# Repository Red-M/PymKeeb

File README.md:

# PymKeeb
## What is this?
I'm getting fed up with the options for keyboards and there isn't anything that I want 100%, everything is a compromise between form factor, customizability and availability.
So I'm making my own keyboard.

## Design choices
I don't want to limit end users on customizing their boards or choosing what they want, so I'll be maximumizing that as much as possible while also giving the option for changing things like the size and layout in forks or derivatives.
I don't want the host device to make choices for the user so limiting things behind having a certain OS is not ok, eg, software that runs on the host device.

## Goals
- USB C input
    - This is just a requirement at this point
- Layout
    - Full size layout with 4 extra switches above the numpad to set for macros
    - Indicator lights need to be above the numbpad
    - Two LEDs per switch, I want extra light
- Switches
    - Hot swap switches
        - Khali hotswaps allow for MX style switches to swap in and out
            - Has a number of switch variants that will fit
- Firmware/Software
    - Firmware only, no host device software at all.
    - Firmware updates should be really simple, no custom software, just drag and drop in DFU or similar
    - CapsLock indicator is in key and matches RGB light of switch
    - All on keyboard with function key similar to ducky keyboards
    - Brightness toggle
    - Macro support
    - NKRO
        - I don't want artifacts or ghosting at all

## Software for designing/building the board
KiCAD, you're going to need KiCAD.
I'm also learning KiCAD so please if you see something I've done that could be done a better way, please file at least an issue or go a head and fix it in a PR.
If it makes sense, I'll merge it in, no questions asked.

## Firmware
This is largely going to depend on what MCU I choose and right now all I know is that the pico or an STMF4 might be the best options.

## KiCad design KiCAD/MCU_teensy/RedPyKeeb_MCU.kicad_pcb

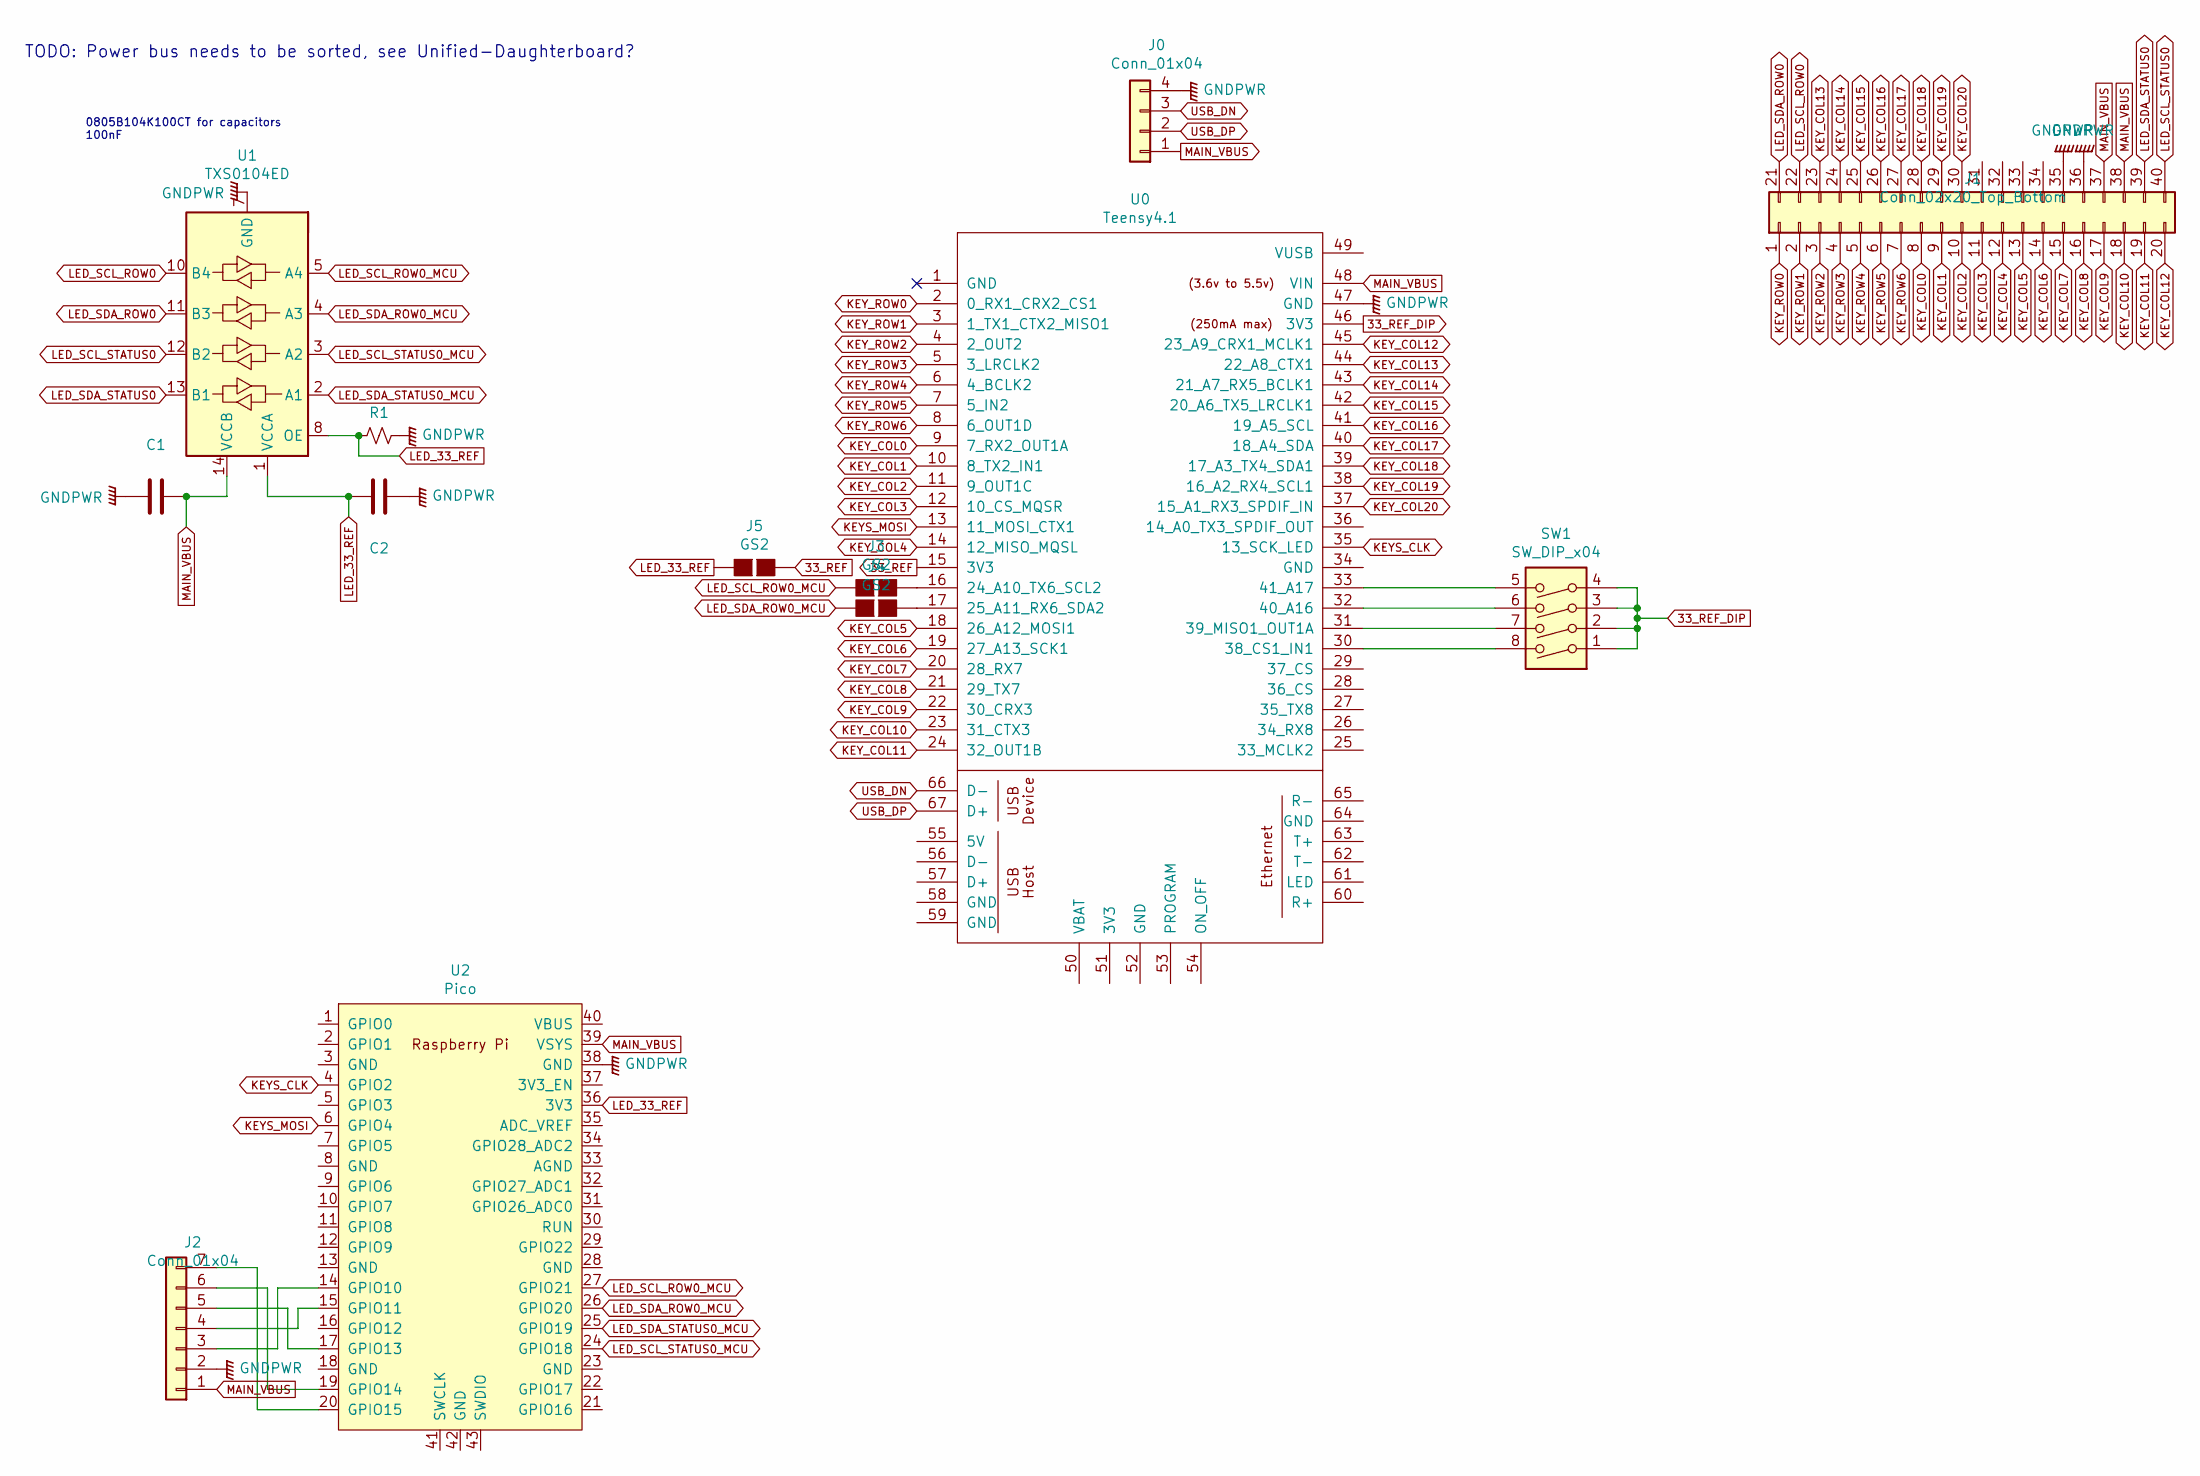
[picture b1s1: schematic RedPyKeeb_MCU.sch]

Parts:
C1, C2: 0805B101K100CT; C_0805_2012Metric_Pad1.18x1.45mm_HandSolder; Mouser No 791-0805B101K100CT
J0: Conn_01x04; JST_EH_S4B-EH_1x04_P2.50mm_Horizontal; Mouser No 485-3955
J1: Conn_02x20_Top_Bottom; PinHeader_2x20_P2.54mm_Vertical_SMD_doublesided; Mouser No 649-95278-102-40LF
J2: Conn_01x04; JST_EH_S7B-EH_1x07_P2.50mm_Horizontal; Mouser No 485-3955
J3, J4, J5: GS2
R1: ERJ-6RED2003V; R_0805_HandSoldering; Mouser No 667-ERJ-6RED2003V
SW1: SW_DIP_x04; SW_DIP_x4_W8.61mm_Slide_LowProfile_bothsides; Mouser No 653-A6SN-4104
U0: Teensy4.1; Teensy41; Mouser No 474-DEV-16771
U1: TXS0104ED; SOIC-14_3.9x8.7mm_P1.27mm; Mouser No 595-TXS0104ED
U2: Pico; RPi_Pico_SMD_TH

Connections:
33_REF: J5.1 (G1), U0.15 (3V3)
33_REF_DIP: SW1.1, SW1.2, SW1.3, SW1.4, U0.46 (3V3)
GNDPWR: C1.1, C2.1, J0.4, J1.35, J1.36, J2.2, R1.1, U0.47 (GND), U1.7 (GND), U2.38 (GND)
KEYS_CLK: U0.35 (13_SCK_LED), U2.4 (GPIO2)
KEYS_MOSI: U0.13 (11_MOSI_CTX1), U2.6 (GPIO4)
KEY_COL0: J1.8, U0.9 (7_RX2_OUT1A)
KEY_COL1: J1.9, U0.10 (8_TX2_IN1)
KEY_COL2: J1.10, U0.11 (9_OUT1C)
KEY_COL3: J1.11, U0.12 (10_CS_MQSR)
KEY_COL4: J1.12, U0.14 (12_MISO_MQSL)
KEY_COL5: J1.13, U0.18 (26_A12_MOSI1)
KEY_COL6: J1.14, U0.19 (27_A13_SCK1)
KEY_COL7: J1.15, U0.20 (28_RX7)
KEY_COL8: J1.16, U0.21 (29_TX7)
KEY_COL9: J1.17, U0.22 (30_CRX3)
KEY_COL10: J1.18, U0.23 (31_CTX3)
KEY_COL11: J1.19, U0.24 (32_OUT1B)
KEY_COL12: J1.20, U0.45 (23_A9_CRX1_MCLK1)
KEY_COL13: J1.23, U0.44 (22_A8_CTX1)
KEY_COL14: J1.24, U0.43 (21_A7_RX5_BCLK1)
KEY_COL15: J1.25, U0.42 (20_A6_TX5_LRCLK1)
KEY_COL16: J1.26, U0.41 (19_A5_SCL)
KEY_COL17: J1.27, U0.40 (18_A4_SDA)
KEY_COL18: J1.28, U0.39 (17_A3_TX4_SDA1)
KEY_COL19: J1.29, U0.38 (16_A2_RX4_SCL1)
KEY_COL20: J1.30, U0.37 (15_A1_RX3_SPDIF_IN)
KEY_ROW0: J1.1, U0.2 (0_RX1_CRX2_CS1)
KEY_ROW1: J1.2, U0.3 (1_TX1_CTX2_MISO1)
KEY_ROW2: J1.3, U0.4 (2_OUT2)
KEY_ROW3: J1.4, U0.5 (3_LRCLK2)
KEY_ROW4: J1.5, U0.6 (4_BCLK2)
KEY_ROW5: J1.6, U0.7 (5_IN2)
KEY_ROW6: J1.7, U0.8 (6_OUT1D)
LED_33_REF: C2.2, J5.2 (G2), R1.2, U1.1 (VCCA), U1.8 (OE), U2.36 (3V3)
LED_SCL_ROW0: J1.22, U1.10 (B4)
LED_SCL_ROW0_MCU: J3.2 (G2), U1.5 (A4), U2.27 (GPIO21)
LED_SCL_STATUS0: J1.40, U1.12 (B2)
LED_SCL_STATUS0_MCU: U1.3 (A2), U2.24 (GPIO18)
LED_SDA_ROW0: J1.21, U1.11 (B3)
LED_SDA_ROW0_MCU: J4.2 (G2), U1.4 (A3), U2.26 (GPIO20)
LED_SDA_STATUS0: J1.39, U1.13 (B1)
LED_SDA_STATUS0_MCU: U1.2 (A1), U2.25 (GPIO19)
MAIN_VBUS: C1.2, J0.1, J1.37, J1.38, J2.1, U0.48 (VIN), U1.14 (VCCB), U2.39 (VSYS)
unnamed: J2.3, U2.14 (GPIO10)
unnamed: J2.4, U2.15 (GPIO11)
unnamed: J2.5, U2.17 (GPIO13)
unnamed: J2.6, U2.19 (GPIO14)
unnamed: J2.7, U2.20 (GPIO15)
unnamed: J3.1 (G1), U0.16 (24_A10_TX6_SCL2)
unnamed: J4.1 (G1), U0.17 (25_A11_RX6_SDA2)
unnamed: SW1.5, U0.33 (41_A17)
unnamed: SW1.6, U0.32 (40_A16)
unnamed: SW1.7, U0.31 (39_MISO1_OUT1A)
unnamed: SW1.8, U0.30 (38_CS1_IN1)
USB_DN: J0.3, U0.66 (D-)
USB_DP: J0.2, U0.67 (D+)

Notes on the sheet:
TODO: Power bus needs to be sorted, see Unified-Daughterboard?
0805B104K100CT for capacitors 100nF

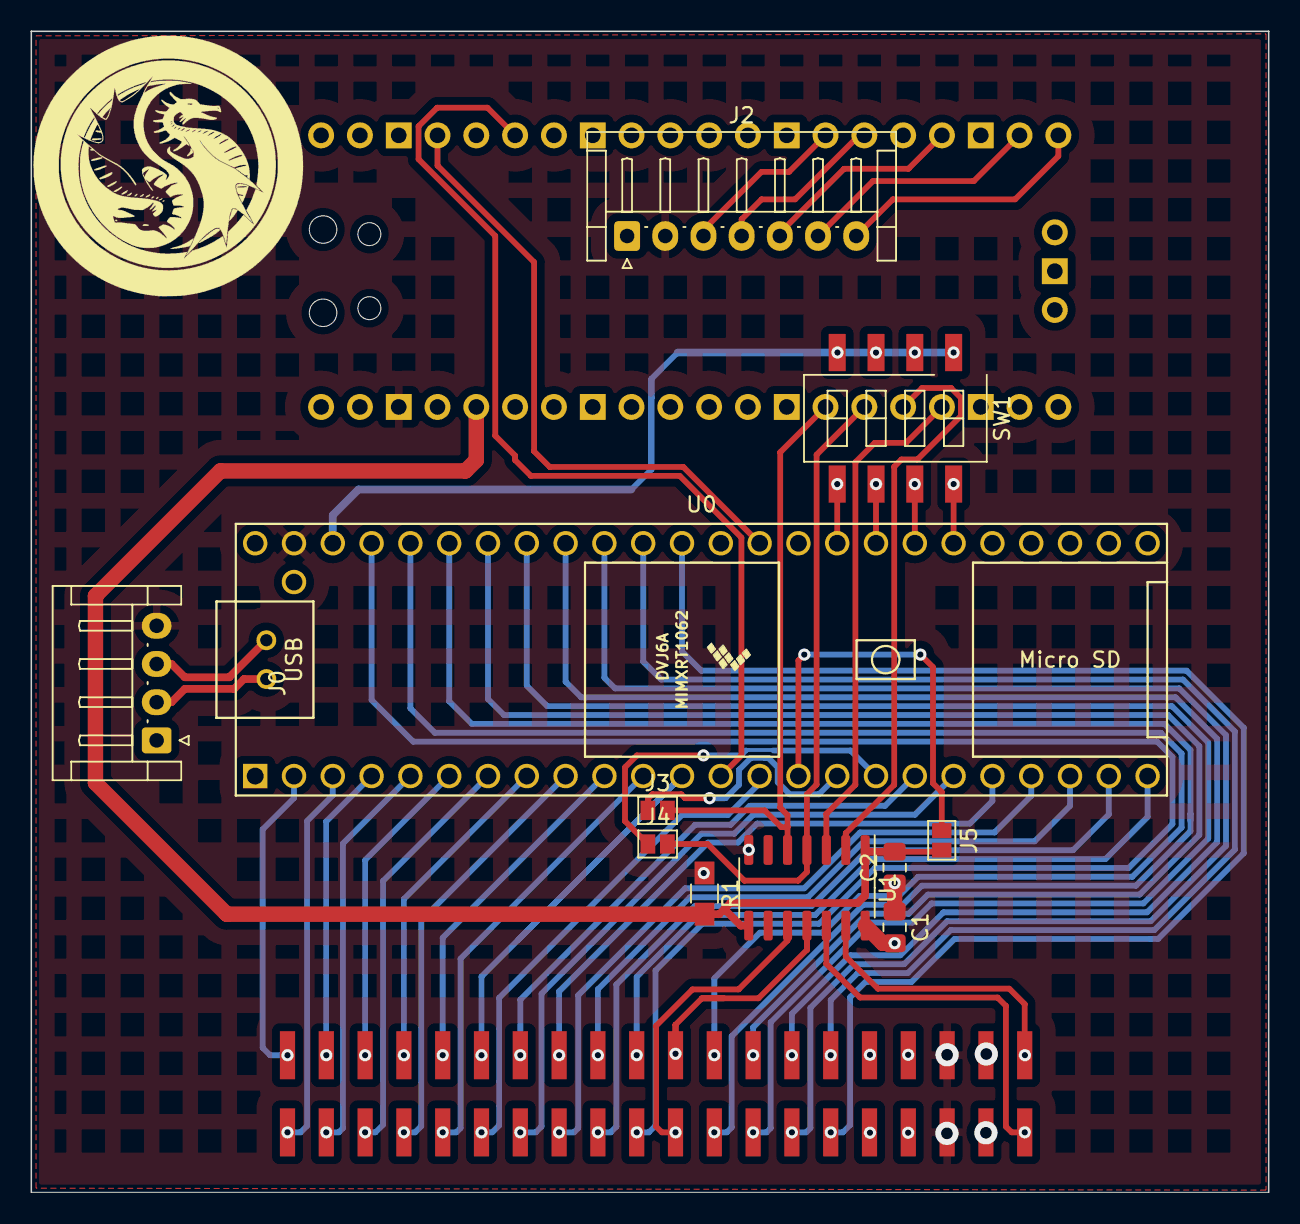
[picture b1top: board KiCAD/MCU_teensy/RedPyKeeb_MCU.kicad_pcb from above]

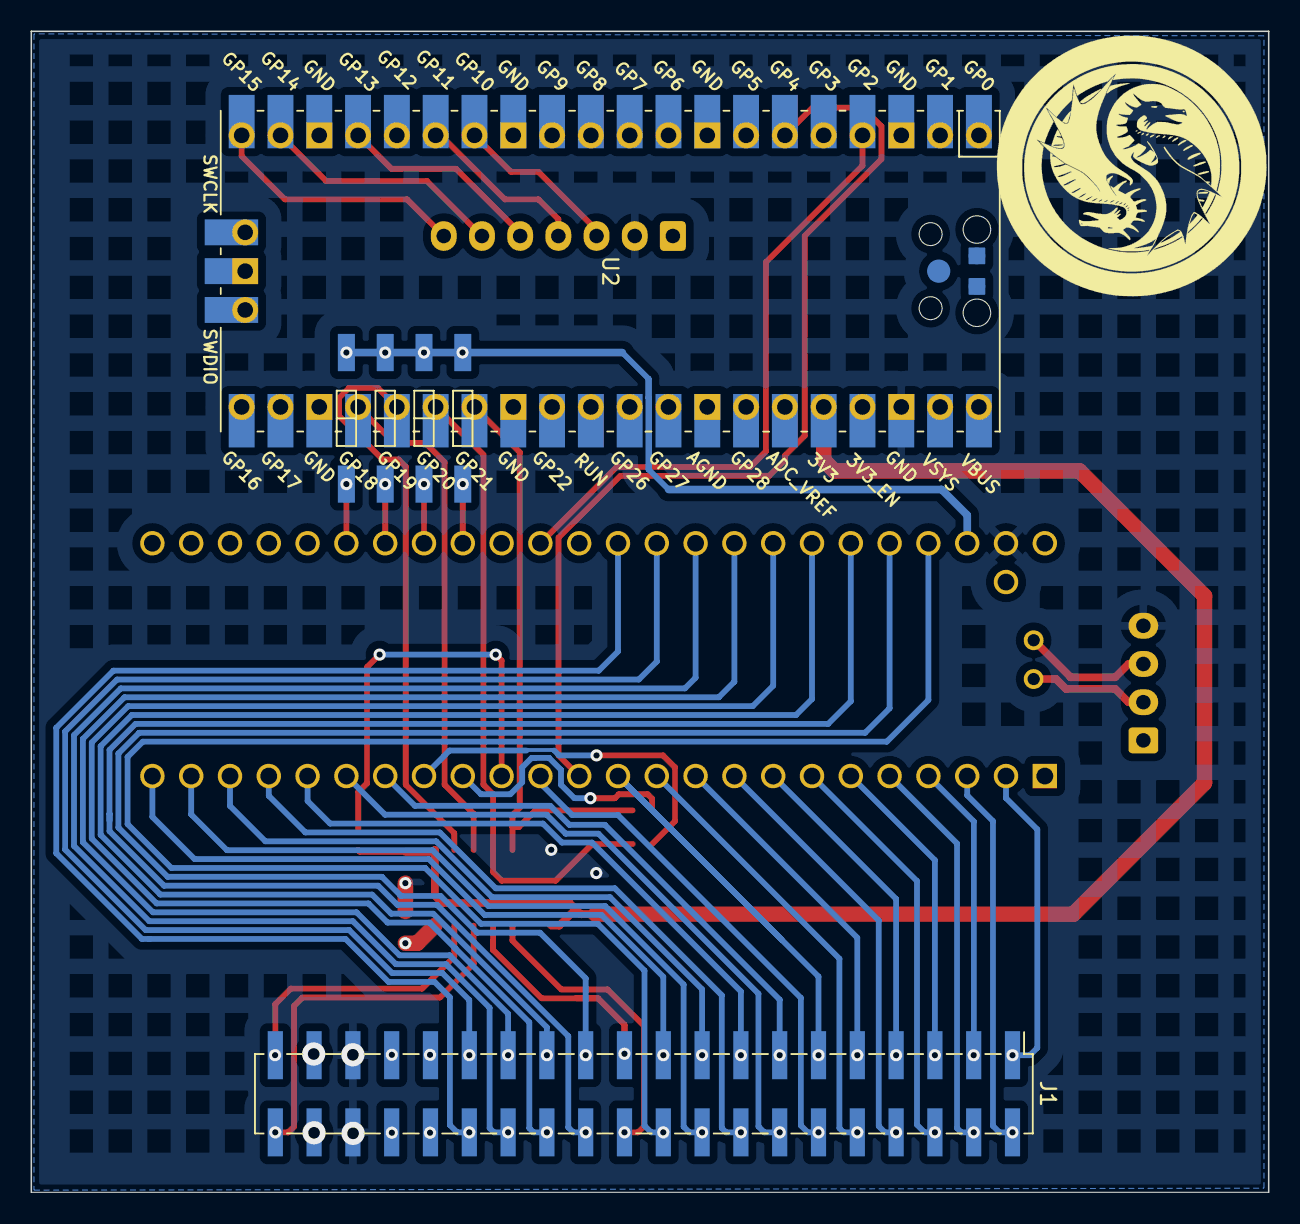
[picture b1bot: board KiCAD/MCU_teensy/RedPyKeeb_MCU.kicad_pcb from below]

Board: 4 copper layers, 81.0 x 76.0 mm, 13 parts (2 on the bottom side), 56 nets.

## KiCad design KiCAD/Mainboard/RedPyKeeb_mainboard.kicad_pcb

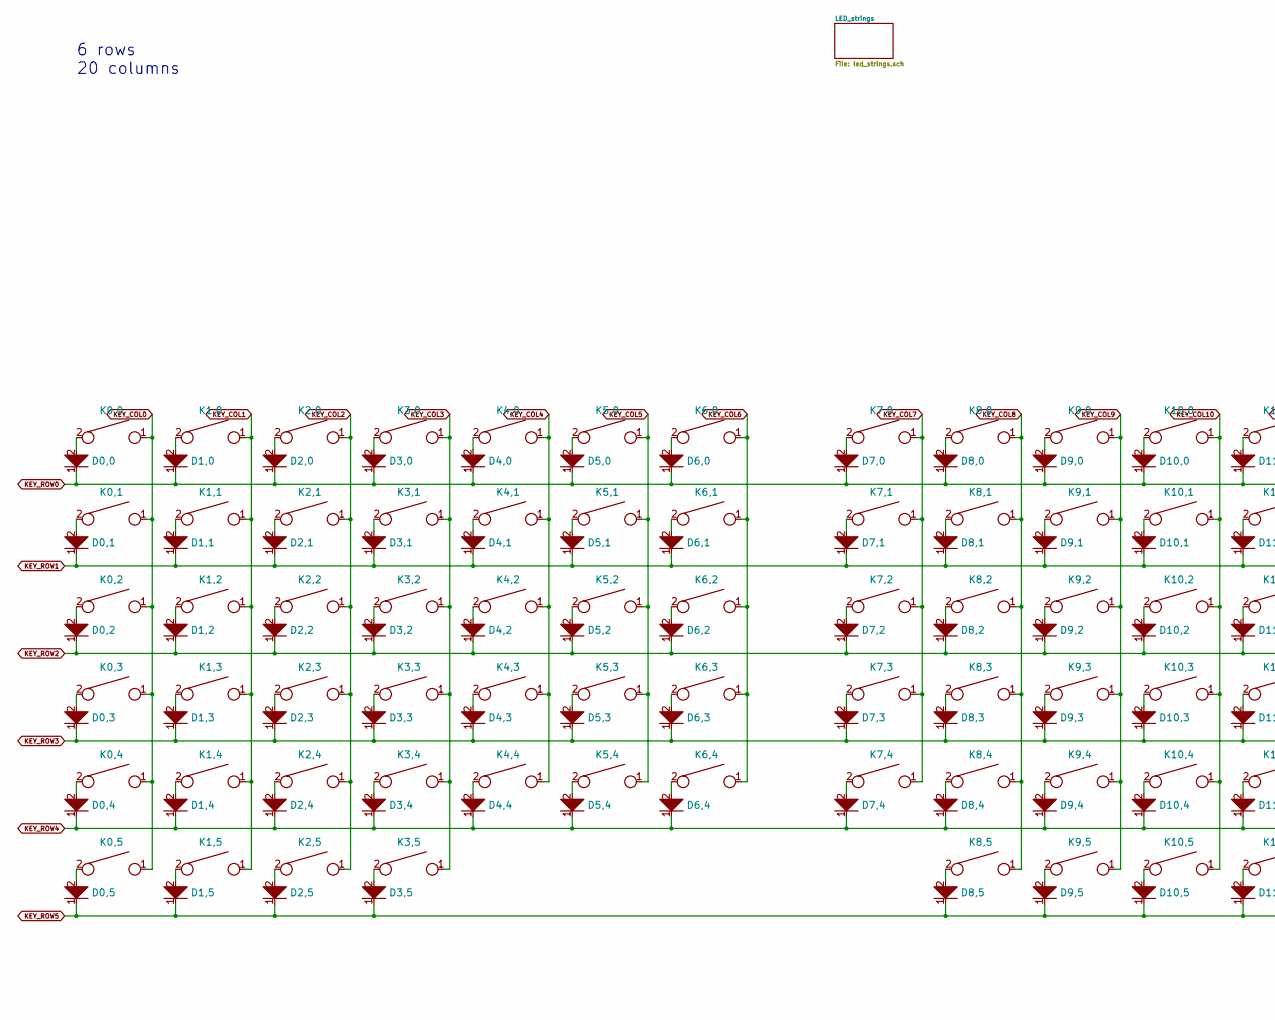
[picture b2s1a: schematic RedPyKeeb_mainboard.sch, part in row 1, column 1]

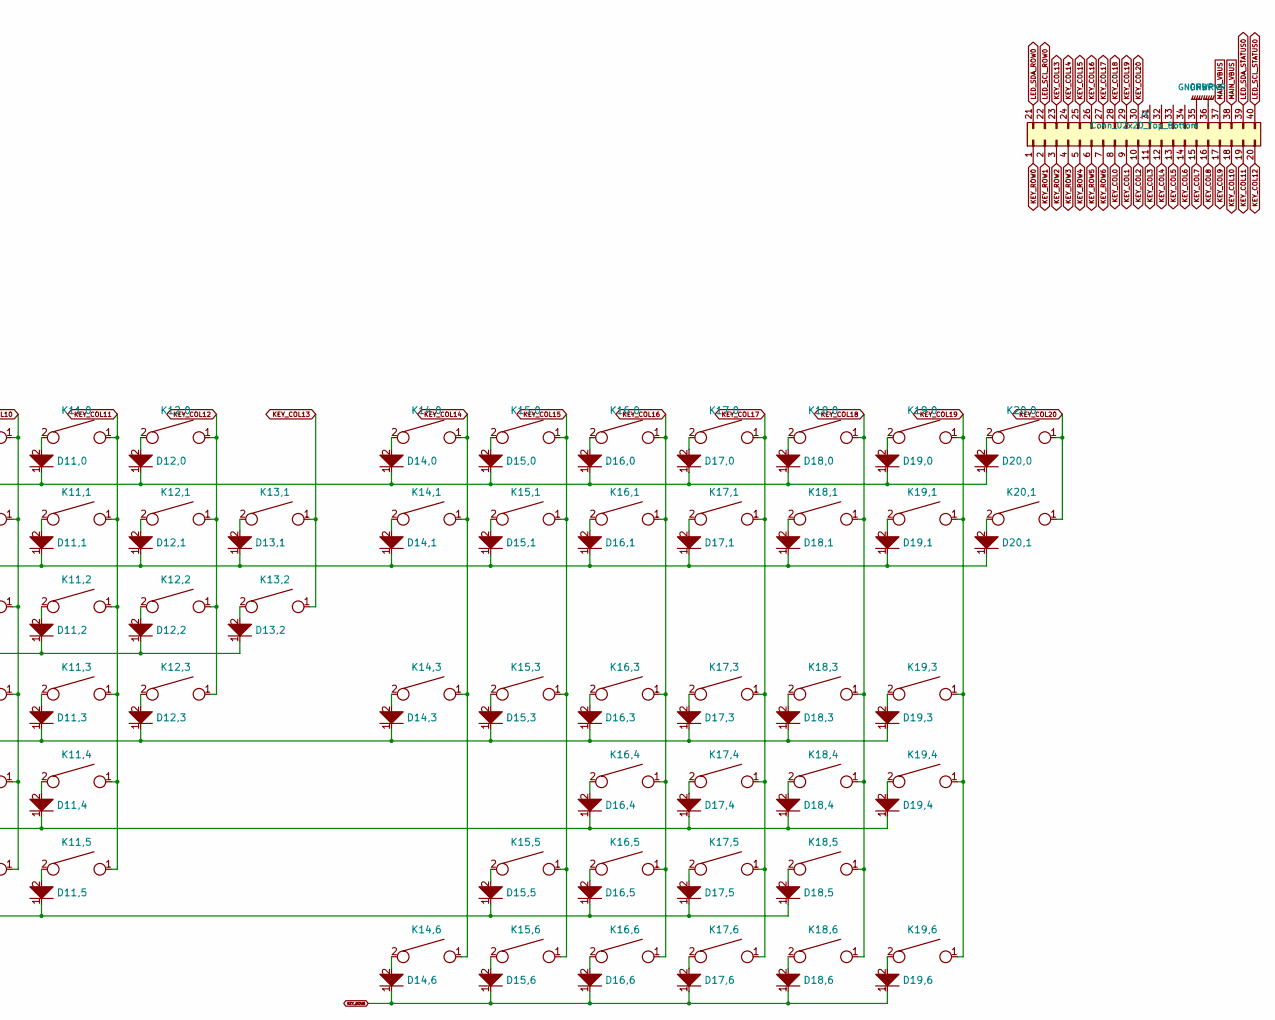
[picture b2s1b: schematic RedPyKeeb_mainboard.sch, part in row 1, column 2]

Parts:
D0,0, D0,1, D0,2, D0,3, D0,4, D0,5, D1,0, D1,1, D1,2, D1,3, D1,4, D1,5, D2,0, D2,1, D2,2, D2,3, D2,4, D2,5, D3,0, D3,1, D3,2, D3,3, D3,4, D3,5, D4,0, D4,1, D4,2, D4,3, D4,4, D5,0, D5,1, D5,2, D5,3, D5,4, D6,0, D6,1, D6,2, D6,3, D6,4, D7,0, D7,1, D7,2, D7,3, D7,4, D8,0, D8,1, D8,2, D8,3, D8,4, D8,5, D9,0, D9,1, D9,2, D9,3, D9,4, D9,5, D10,0, D10,1, D10,2, D10,3, D10,4, D10,5, D11,0, D11,1, D11,2, D11,3, D11,4, D11,5, D12,0, D12,1, D12,2, D12,3, D13,1, D13,2, D14,0, D14,1, D14,3, D14,6, D15,0, D15,1, D15,3, D15,5, D15,6, D16,0, D16,1, D16,3, D16,4, D16,5, D16,6, D17,0, D17,1, D17,3, D17,4, D17,5, D17,6, D18,0, D18,1, D18,3, D18,4, D18,5, D18,6, D19,0, D19,1, D19,3, D19,4, D19,6, D20,0, D20,1: 1N4148W-7-F; D_SOD123_axial; Mouser No 621-1N4148W-F
J1: Conn_02x20_Top_Bottom; PinHeader_2x20_P2.54mm_Vertical_SMD_doublesided; Mouser No 200-SSM120LMDVBE
K0,0, K0,1, K1,0, K1,1, K1,2, K1,3, K1,4, K2,0, K2,1, K2,2, K2,3, K2,4, K3,0, K3,1, K3,2, K3,3, K3,4, K4,0, K4,1, K4,2, K4,3, K4,4, K5,0, K5,1, K5,2, K5,3, K5,4, K6,0, K6,1, K6,2, K6,3, K6,4, K7,0, K7,1, K7,2, K7,3, K7,4, K8,0, K8,1, K8,2, K8,3, K8,4, K9,0, K9,1, K9,2, K9,3, K9,4, K10,0, K10,1, K10,2, K10,3, K10,4, K11,0, K11,1, K11,2, K11,3, K12,0, K12,1, K12,2, K14,0, K14,1, K14,3, K14,6, K15,0, K15,1, K15,3, K15,5, K15,6, K16,0, K16,1, K16,3, K16,4, K16,5, K16,6, K17,0, K17,1, K17,3, K17,4, K17,5, K18,0, K18,1, K18,3, K18,4, K18,5, K18,6, K19,0, K19,1, K19,3, K20,0, K20,1: SW_Hotswap_Kailh_1.00u
K0,2, K13,2: SW_Hotswap_Kailh_1.50u
K0,3: SW_Hotswap_Kailh_1.75u
K0,4, K12,3: SW_Hotswap_Kailh_2.25u
K0,5, K1,5, K2,5, K8,5, K9,5, K10,5, K11,5: SW_Hotswap_Kailh_1.25u
K3,5: SW_Hotswap_Kailh_6.25u
K11,4: SW_Hotswap_Kailh_2.75u
K13,1, K17,6: SW_Hotswap_Kailh_2.00u
K19,4, K19,6: SW_Hotswap_Kailh_2.00u_Rotated

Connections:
GNDPWR: J1.35, J1.36; also elsewhere on the board
KEY_COL0: J1.8, K0,0.1, K0,1.1, K0,2.1, K0,3.1, K0,4.1, K0,5.1
KEY_COL1: J1.9, K1,0.1, K1,1.1, K1,2.1, K1,3.1, K1,4.1, K1,5.1
KEY_COL2: J1.10, K2,0.1, K2,1.1, K2,2.1, K2,3.1, K2,4.1, K2,5.1
KEY_COL3: J1.11, K3,0.1, K3,1.1, K3,2.1, K3,3.1, K3,4.1, K3,5.1
KEY_COL4: J1.12, K4,0.1, K4,1.1, K4,2.1, K4,3.1, K4,4.1
KEY_COL5: J1.13, K5,0.1, K5,1.1, K5,2.1, K5,3.1, K5,4.1
KEY_COL6: J1.14, K6,0.1, K6,1.1, K6,2.1, K6,3.1, K6,4.1
KEY_COL7: J1.15, K7,0.1, K7,1.1, K7,2.1, K7,3.1, K7,4.1
KEY_COL8: J1.16, K8,0.1, K8,1.1, K8,2.1, K8,3.1, K8,4.1, K8,5.1
KEY_COL9: J1.17, K9,0.1, K9,1.1, K9,2.1, K9,3.1, K9,4.1, K9,5.1
KEY_COL10: J1.18, K10,0.1, K10,1.1, K10,2.1, K10,3.1, K10,4.1, K10,5.1
KEY_COL11: J1.19, K11,0.1, K11,1.1, K11,2.1, K11,3.1, K11,4.1, K11,5.1
KEY_COL12: J1.20, K12,0.1, K12,1.1, K12,2.1, K12,3.1
KEY_COL13: J1.23, K13,1.1, K13,2.1
KEY_COL14: J1.24, K14,0.1, K14,1.1, K14,3.1, K14,6.1
KEY_COL15: J1.25, K15,0.1, K15,1.1, K15,3.1, K15,5.1, K15,6.1
KEY_COL16: J1.26, K16,0.1, K16,1.1, K16,3.1, K16,4.1, K16,5.1, K16,6.1
KEY_COL17: J1.27, K17,0.1, K17,1.1, K17,3.1, K17,4.1, K17,5.1, K17,6.1
KEY_COL18: J1.28, K18,0.1, K18,1.1, K18,3.1, K18,4.1, K18,5.1, K18,6.1
KEY_COL19: J1.29, K19,0.1, K19,1.1, K19,3.1, K19,4.1, K19,6.1
KEY_COL20: J1.30, K20,0.1, K20,1.1
KEY_ROW0: D0,0.1, D1,0.1, D2,0.1, D3,0.1, D4,0.1, D5,0.1, D6,0.1, D7,0.1, D8,0.1, D9,0.1, D10,0.1, D11,0.1, D12,0.1, D14,0.1, D15,0.1, D16,0.1, D17,0.1, D18,0.1, D19,0.1, D20,0.1, J1.1
KEY_ROW1: D0,1.1, D1,1.1, D2,1.1, D3,1.1, D4,1.1, D5,1.1, D6,1.1, D7,1.1, D8,1.1, D9,1.1, D10,1.1, D11,1.1, D12,1.1, D13,1.1, D14,1.1, D15,1.1, D16,1.1, D17,1.1, D18,1.1, D19,1.1, D20,1.1, J1.2
KEY_ROW2: D0,2.1, D1,2.1, D2,2.1, D3,2.1, D4,2.1, D5,2.1, D6,2.1, D7,2.1, D8,2.1, D9,2.1, D10,2.1, D11,2.1, D12,2.1, D13,2.1, J1.3
KEY_ROW3: D0,3.1, D1,3.1, D2,3.1, D3,3.1, D4,3.1, D5,3.1, D6,3.1, D7,3.1, D8,3.1, D9,3.1, D10,3.1, D11,3.1, D12,3.1, D14,3.1, D15,3.1, D16,3.1, D17,3.1, D18,3.1, D19,3.1, J1.4
KEY_ROW4: D0,4.1, D1,4.1, D2,4.1, D3,4.1, D4,4.1, D5,4.1, D6,4.1, D7,4.1, D8,4.1, D9,4.1, D10,4.1, D11,4.1, D16,4.1, D17,4.1, D18,4.1, D19,4.1, J1.5
KEY_ROW5: D0,5.1, D1,5.1, D2,5.1, D3,5.1, D8,5.1, D9,5.1, D10,5.1, D11,5.1, D15,5.1, D16,5.1, D17,5.1, D18,5.1, J1.6
KEY_ROW6: D14,6.1, D15,6.1, D16,6.1, D17,6.1, D18,6.1, D19,6.1, J1.7
LED_SCL_ROW0: J1.22; also elsewhere on the board
LED_SCL_STATUS0: J1.40; also elsewhere on the board
LED_SDA_ROW0: J1.21; also elsewhere on the board
LED_SDA_STATUS0: J1.39; also elsewhere on the board
MAIN_VBUS: J1.37, J1.38; also elsewhere on the board
unnamed: D0,0.2, K0,0.2
unnamed: D0,1.2, K0,1.2
unnamed: D0,2.2, K0,2.2
unnamed: D0,3.2, K0,3.2
unnamed: D0,4.2, K0,4.2
unnamed: D0,5.2, K0,5.2
unnamed: D1,0.2, K1,0.2
unnamed: D1,1.2, K1,1.2
unnamed: D1,2.2, K1,2.2
unnamed: D1,3.2, K1,3.2
unnamed: D1,4.2, K1,4.2
unnamed: D1,5.2, K1,5.2
unnamed: D2,0.2, K2,0.2
unnamed: D2,1.2, K2,1.2
unnamed: D2,2.2, K2,2.2
unnamed: D2,3.2, K2,3.2
unnamed: D2,4.2, K2,4.2
unnamed: D2,5.2, K2,5.2
unnamed: D3,0.2, K3,0.2
unnamed: D3,1.2, K3,1.2
unnamed: D3,2.2, K3,2.2
unnamed: D3,3.2, K3,3.2
unnamed: D3,4.2, K3,4.2
unnamed: D3,5.2, K3,5.2
unnamed: D4,0.2, K4,0.2
unnamed: D4,1.2, K4,1.2
unnamed: D4,2.2, K4,2.2
unnamed: D4,3.2, K4,3.2
unnamed: D4,4.2, K4,4.2
unnamed: D5,0.2, K5,0.2
unnamed: D5,1.2, K5,1.2
unnamed: D5,2.2, K5,2.2
unnamed: D5,3.2, K5,3.2
unnamed: D5,4.2, K5,4.2
unnamed: D6,0.2, K6,0.2
unnamed: D6,1.2, K6,1.2
unnamed: D6,2.2, K6,2.2
unnamed: D6,3.2, K6,3.2
unnamed: D6,4.2, K6,4.2
unnamed: D7,0.2, K7,0.2
unnamed: D7,1.2, K7,1.2
unnamed: D7,2.2, K7,2.2
unnamed: D7,3.2, K7,3.2
unnamed: D7,4.2, K7,4.2
unnamed: D8,0.2, K8,0.2
unnamed: D8,1.2, K8,1.2
unnamed: D8,2.2, K8,2.2
unnamed: D8,3.2, K8,3.2
unnamed: D8,4.2, K8,4.2
unnamed: D8,5.2, K8,5.2
unnamed: D9,0.2, K9,0.2
unnamed: D9,1.2, K9,1.2
unnamed: D9,2.2, K9,2.2
unnamed: D9,3.2, K9,3.2
unnamed: D9,4.2, K9,4.2
unnamed: D9,5.2, K9,5.2
unnamed: D10,0.2, K10,0.2
unnamed: D10,1.2, K10,1.2
unnamed: D10,2.2, K10,2.2
unnamed: D10,3.2, K10,3.2
unnamed: D10,4.2, K10,4.2
unnamed: D10,5.2, K10,5.2
unnamed: D11,0.2, K11,0.2
unnamed: D11,1.2, K11,1.2
unnamed: D11,2.2, K11,2.2
unnamed: D11,3.2, K11,3.2
unnamed: D11,4.2, K11,4.2
unnamed: D11,5.2, K11,5.2
unnamed: D12,0.2, K12,0.2
unnamed: D12,1.2, K12,1.2
unnamed: D12,2.2, K12,2.2
unnamed: D12,3.2, K12,3.2
unnamed: D13,1.2, K13,1.2
unnamed: D13,2.2, K13,2.2
unnamed: D14,0.2, K14,0.2
unnamed: D14,1.2, K14,1.2
unnamed: D14,3.2, K14,3.2
unnamed: D14,6.2, K14,6.2
unnamed: D15,0.2, K15,0.2
unnamed: D15,1.2, K15,1.2
unnamed: D15,3.2, K15,3.2
unnamed: D15,5.2, K15,5.2
unnamed: D15,6.2, K15,6.2
unnamed: D16,0.2, K16,0.2
unnamed: D16,1.2, K16,1.2
unnamed: D16,3.2, K16,3.2
unnamed: D16,4.2, K16,4.2
unnamed: D16,5.2, K16,5.2
unnamed: D16,6.2, K16,6.2
unnamed: D17,0.2, K17,0.2
unnamed: D17,1.2, K17,1.2
unnamed: D17,3.2, K17,3.2
unnamed: D17,4.2, K17,4.2
unnamed: D17,5.2, K17,5.2
unnamed: D17,6.2, K17,6.2
unnamed: D18,0.2, K18,0.2
unnamed: D18,1.2, K18,1.2
unnamed: D18,3.2, K18,3.2
unnamed: D18,4.2, K18,4.2
unnamed: D18,5.2, K18,5.2
unnamed: D18,6.2, K18,6.2
unnamed: D19,0.2, K19,0.2
unnamed: D19,1.2, K19,1.2
unnamed: D19,3.2, K19,3.2
unnamed: D19,4.2, K19,4.2
unnamed: D19,6.2, K19,6.2
unnamed: D20,0.2, K20,0.2
unnamed: D20,1.2, K20,1.2

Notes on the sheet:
6 rows 20 columns
